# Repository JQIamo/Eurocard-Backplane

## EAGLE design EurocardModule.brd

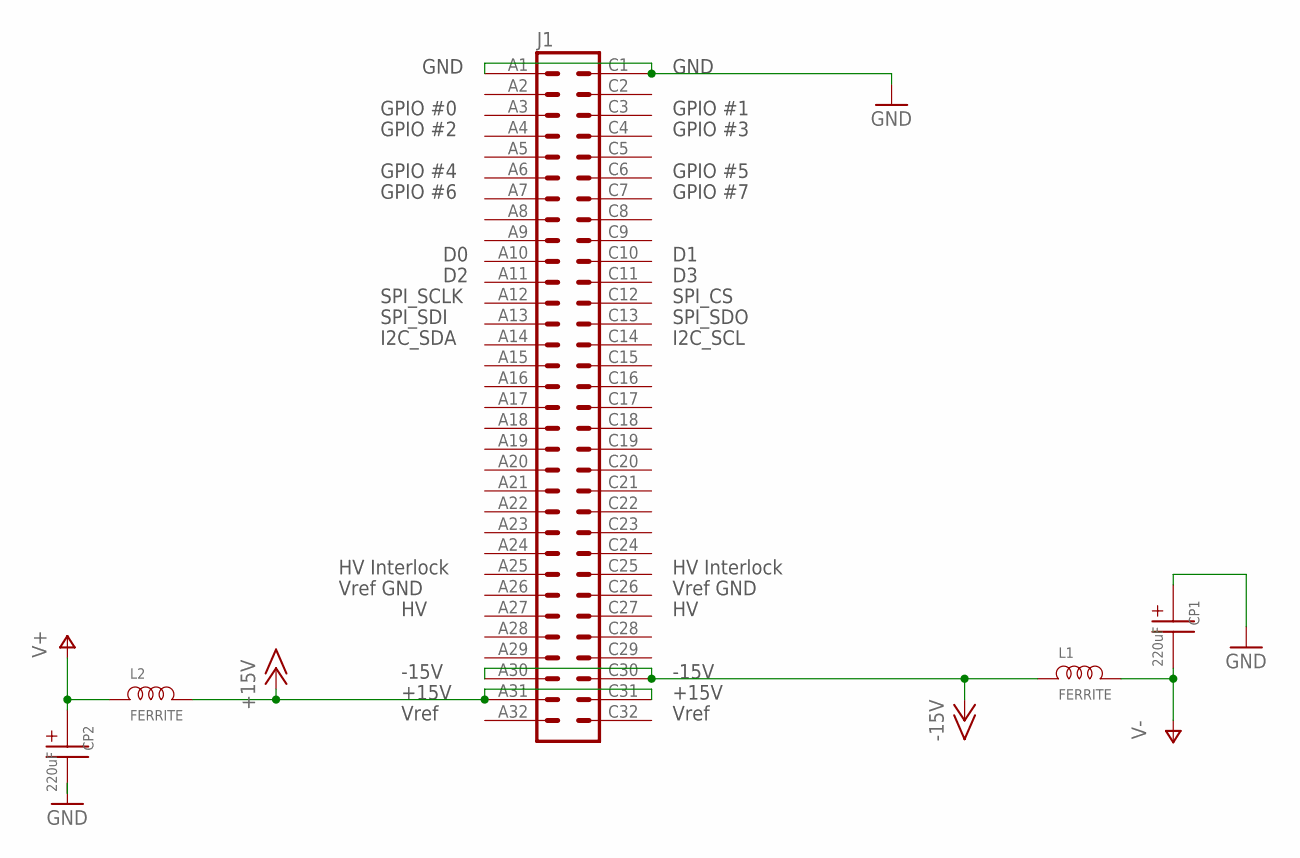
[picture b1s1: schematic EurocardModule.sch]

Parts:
CP1, CP2: 220uF; PANASONIC_F
J1: VG64P
L1, L2: FERRITE; 0805; PARTNO 445-5223-1-ND

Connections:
+15V: J1.A31, J1.C31, L2.2
-15V: J1.A30, J1.C30, L1.1
GND: CP1.+, CP2.-, J1.A1, J1.C1
V+: CP2.+, L2.1
V-: CP1.-, L1.2

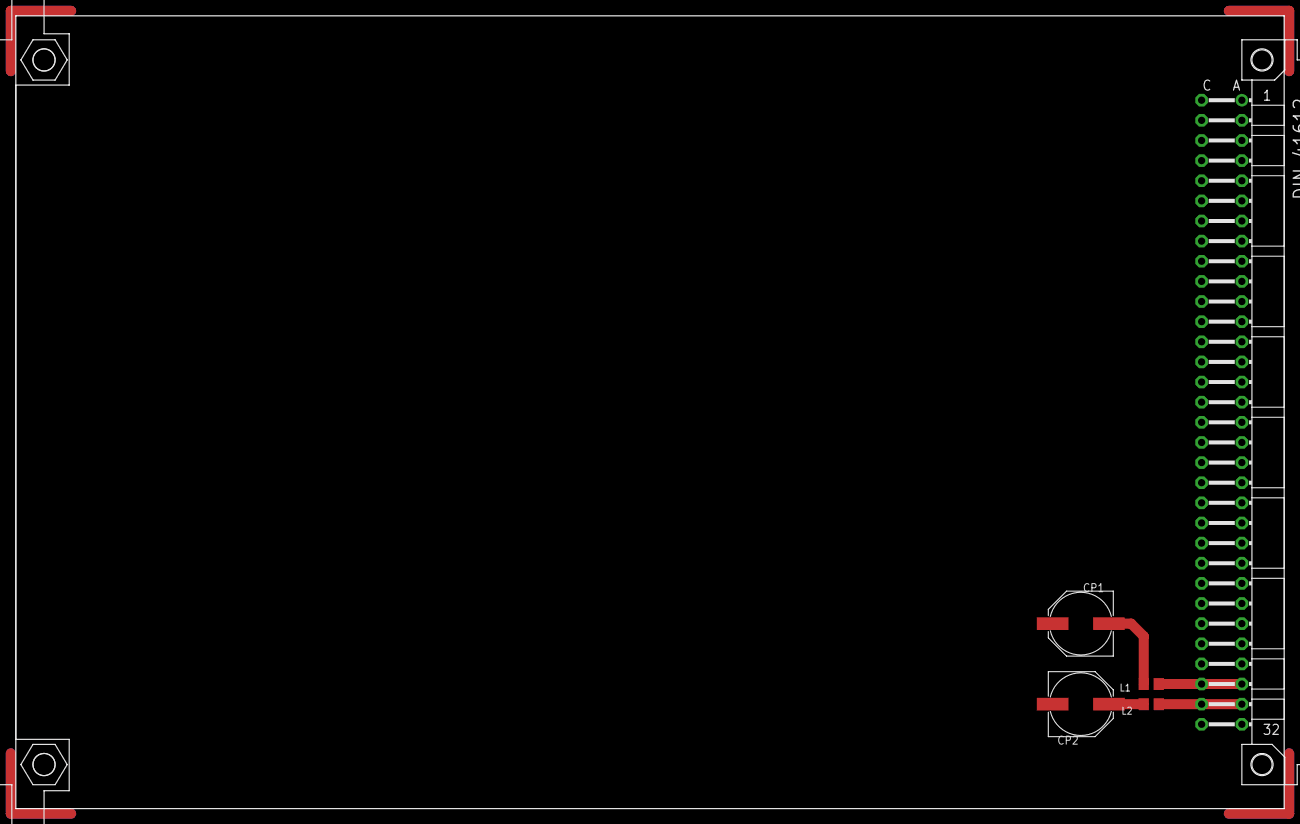
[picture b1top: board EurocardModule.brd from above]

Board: 2 copper layers, 160.0 x 100.0 mm, 5 parts (0 on the bottom side), 5 nets.
